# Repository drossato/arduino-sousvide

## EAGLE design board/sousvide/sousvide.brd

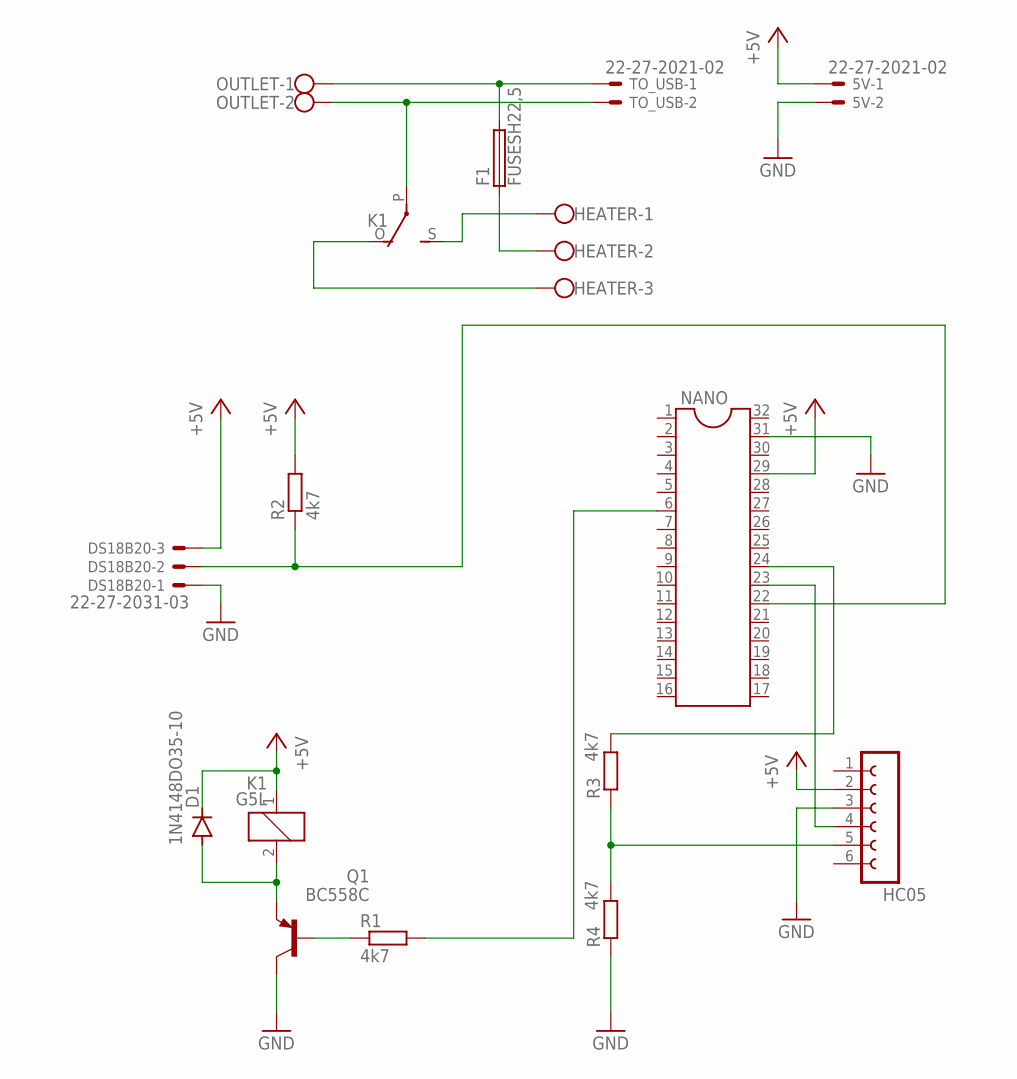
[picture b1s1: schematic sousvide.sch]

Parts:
5V: 22-27-2021-02; 6410-02
D1: 1N4148DO35-10; DO35-10
DS18B20: 22-27-2031-03; 6410-03
F1: FUSESH22,5; SH22,5
HC05: FE06-1; FE06
HEATER: W237-103
K1: G5L; G5LE
NANO: DIL32
OUTLET: W237-102
Q1: BC558C; TO92-EBC
R1, R2, R3, R4: 4k7; 0204/7
TO_USB: 22-27-2021-02; 6410-02

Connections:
+5V: 5V.1, D1.C, DS18B20.3, HC05.2, K1.1, NANO.29, R2.2
BTRX: HC05.5, R3.1, R4.2
GND: 5V.2, DS18B20.1, HC05.3, NANO.31, Q1.C, R4.1
unnamed: F1.2, OUTLET.1, TO_USB.1
unnamed: K1.P, OUTLET.2, TO_USB.2
unnamed: D1.A, K1.2, Q1.E
unnamed: Q1.B, R1.1
unnamed: F1.1, HEATER.2
NANORX: HC05.4, NANO.23
NANOTX: NANO.24, R3.2
ONEWIRE: DS18B20.2, NANO.22, R2.1
RELAYCONTROL: NANO.6, R1.2
RELAYNA: HEATER.1, K1.S
RELAYNC: HEATER.3, K1.O

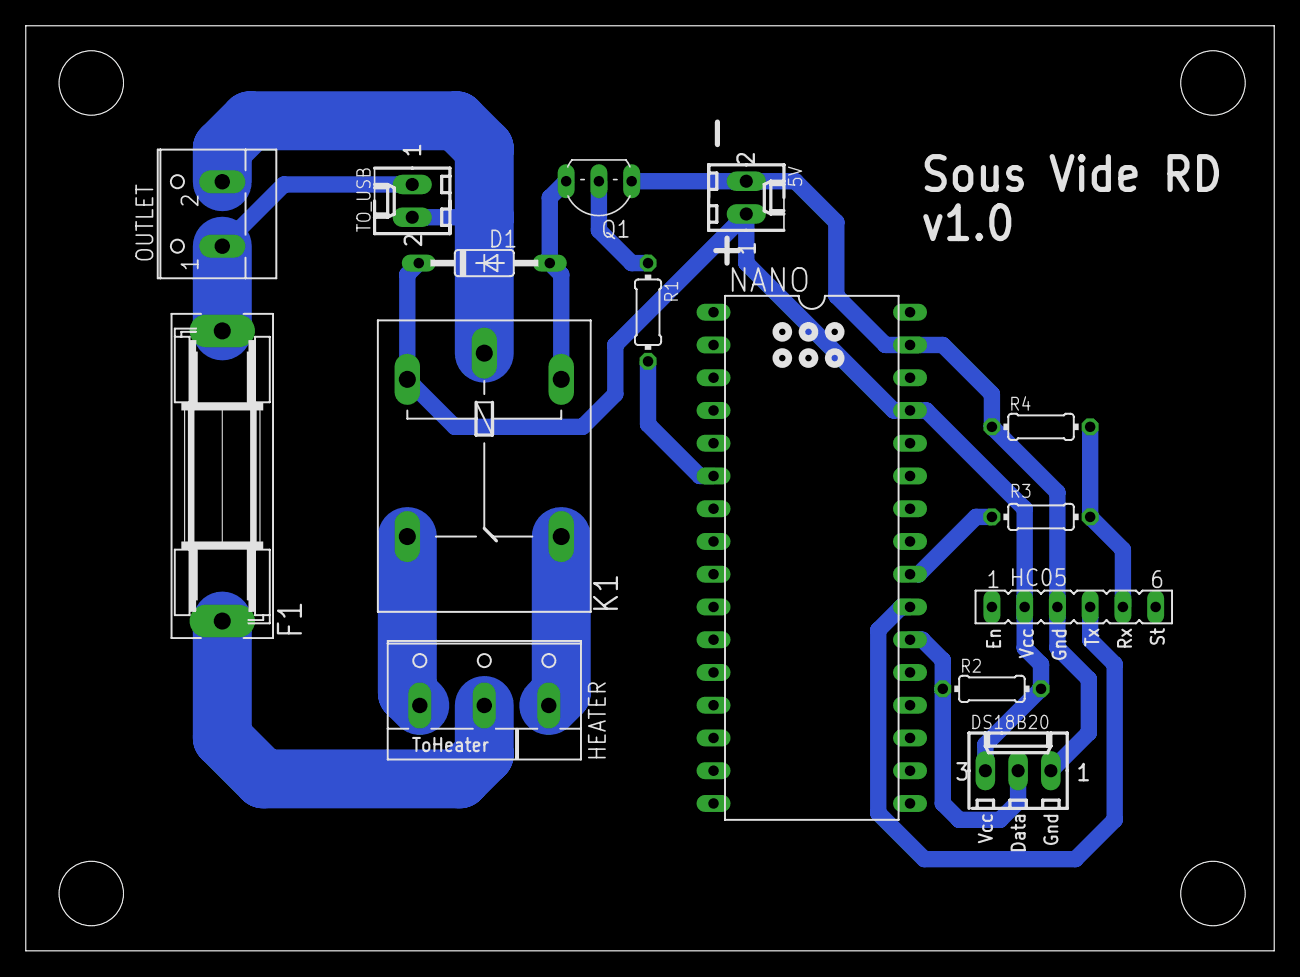
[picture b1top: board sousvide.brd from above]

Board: 2 copper layers, 96.8 x 71.7 mm, 15 parts (0 on the bottom side), 14 nets.

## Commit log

2019-05-29 Main file added
    Adding main file. Control functionality is complete, albeit with a hard-coded fixed setpoint.
2019-05-29 Folder structure correction
2019-06-04 Correction in measurements
    Now does not increase measure counter if the measurement was invalid
2019-06-04 Relay safety and PID delay
    - No more 30s delay between turning on and PID starting
    - Relay now switches off if communication with temperature sensor is lost
2019-06-07 Sous Vide PCB Added
    Made using Autodesk EAGLE 9
2019-06-07 Create BOM.txt
    BOM for 2 boards
2019-06-10 Board change
    Changed design so the BT module can fit over the board
2019-06-10 New fuse
    Updating fuse holder footprint to match the one we bought
2019-06-11 Board corrections
    Changed relay transistor to PNP, to avoid turning the heater on during reset and with the device turned off.
    Changed transistor base resistor to 4k7. Old value did not allowed enough current to switch the relay.
2019-06-11 Updated pins
    Changed pins in the arduino code to match the new board. Added Bluetooth.
2019-06-11 Bluetooth protocol
    First version of the bluetooth protocol to communicate with the controller app.
2019-06-12 Connectors update
    Changing connectors to better match physical ones. Created better labels in silk layer.
2019-06-18 Update code for PNP
    Updating code to match the PNP transistor used in the board to drive current to the relay. Old version was NPN.
2019-06-24 Integral Windup
    New integral windup strategies implemented in the PID controller, based on https://ieeexplore.ieee.org/stamp/stamp.jsp?tp=&arnumber=1193605
    Default is set as back-calculation, alternative is clamping. Needs tests and recalibration.
2019-06-25 PID update
    Changed windup to clamping, and updated the gains.
2020-03-28 Report
    Added the "R" command, that responds with a report containing, temperature, setpoint, state, sensor function, uptime.
2022-06-08 Report and reset resume
    - Auto continuation after unintended short reset
    - New command - R (report) - show more information like setpoint and uptime.
2022-06-09 Sensor Resolution Change
    Newer sensors have been slower, so the resolution has been lowered to compensate.
